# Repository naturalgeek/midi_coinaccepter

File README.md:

Prototype:
http://ketahole.de/midicoin.gif

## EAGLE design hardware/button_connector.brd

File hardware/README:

This is a dirty drawed adaptor PCB
to use 8 Buttons at one Analog Input of the Arduino.

Connect the PCBs "LINK" pins to the Arduino.

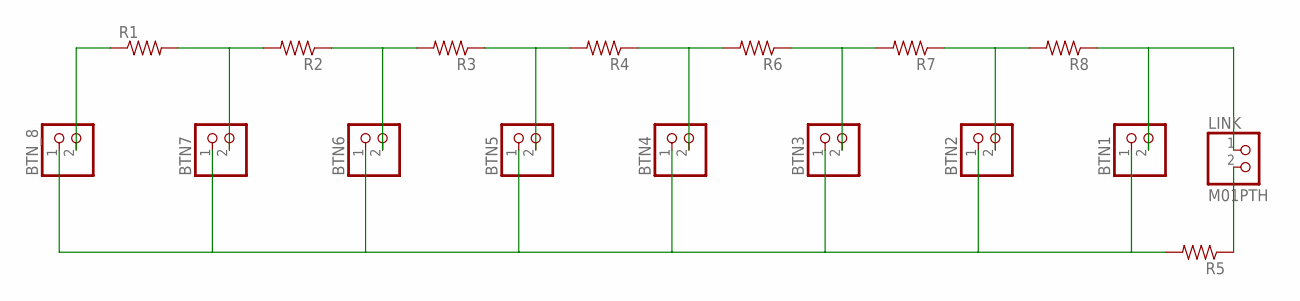
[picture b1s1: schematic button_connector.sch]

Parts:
BTN1, BTN2, BTN3, BTN4, BTN5, BTN6, BTN7: PINHD-1X2; 1X02
BTN_8: PINHD-1X2; 1X02
LINK: M01PTH; 1X02
R1, R2, R3, R4, R5, R6, R7, R8: RESISTORPTH1; AXIAL-0.3

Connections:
A5: BTN1.2, LINK.1, R8.P$1 (1)
GND: BTN1.1, BTN2.1, BTN3.1, BTN4.1, BTN5.1, BTN6.1, BTN7.1, BTN_8.1, R5.P$2 (2)
unnamed: LINK.2, R5.P$1 (1)
unnamed: BTN_8.2, R1.P$1 (1)
unnamed: BTN7.2, R1.P$2 (2), R2.P$2 (2)
unnamed: BTN6.2, R2.P$1 (1), R3.P$2 (2)
unnamed: BTN5.2, R3.P$1 (1), R4.P$2 (2)
unnamed: BTN4.2, R4.P$1 (1), R6.P$2 (2)
unnamed: BTN3.2, R6.P$1 (1), R7.P$2 (2)
unnamed: BTN2.2, R7.P$1 (1), R8.P$2 (2)

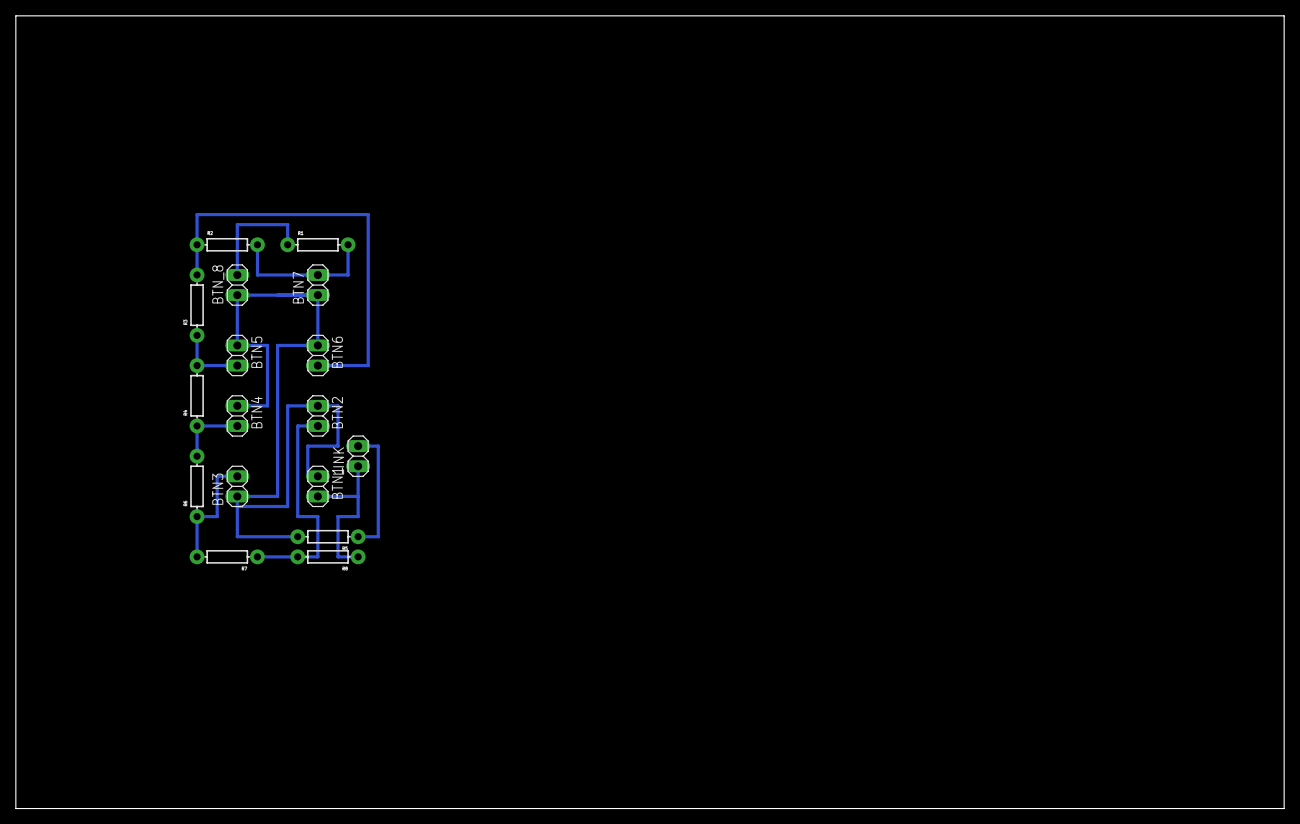
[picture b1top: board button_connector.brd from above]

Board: 2 copper layers, 160.0 x 100.0 mm, 17 parts (0 on the bottom side), 10 nets.

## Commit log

2018-04-22 First Test
2018-04-22 added hardware
2018-04-22 first version with catcher effect
2018-04-22 added midi support (not tested)
2018-04-22 added debug options: press while booting: 1: serial debug: 2: serial debug+fake coins
2018-04-22 added prototype gif
2018-04-22 added README
2018-05-28 fix button resistors
